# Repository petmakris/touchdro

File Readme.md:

# Parts

* ESP32 DEVKIT V1
    - https://www.aliexpress.us/item/2255800094862861.html

* Micro USB Connector Breakout 

  - https://www.aliexpress.com/item/1005006088838882.html

* ±5% 100V 100nF -40℃~+110℃ Metallized Polyester Plugin,P=5mm

    - [C3034534](https://www.lcsc.com/product-detail/Film-Capacitors_KNSCHA-MEB104J100V82CB0018_C3034534.html)

* 47uF 50V ±20% 180mA@100kHz Plugin,D6.3xL12mm 

    - [C2831773](https://www.lcsc.com/product-detail/Aluminum-Electrolytic-Capacitors-Leaded_KNSCHA-03EC0571_C2831773.html)

* Metal Film Resistors 4.7kΩ 250mW ±100ppm/℃ ±1%
 
    - [C119339](https://www.lcsc.com/product-detail/Through-Hole-Resistors_CCO-Chian-Chia-Elec-MF1-4W-4-7K-1-T_C119339.html)

* Metal Film Resistors 47kΩ 250mW ±50ppm/℃ ±1%

    - [C410613](https://www.lcsc.com/product-detail/Through-Hole-Resistors_TyoHM-RN-1-4W-47K-F-T-B-A1_C410613.html)

* SN74HC14N Schmitt Trigger 6 21ns@6V,50pF 2uA 2V~6V DIP-14 Inverters ROHS

    - [C2907](https://www.lcsc.com/product-detail/Inverters_Texas-Instruments-SN74HC14N_C2907.html)

# Micro USB Breakout

# ESP32 DevKit V1

# Firmware

```bash
esptool.py --chip esp32 --port COM5 --baud 460800 --before default_reset --after hard_reset write_flash --flash_mode dio --flash_size detect --flash_freq 40m 0x1000 bootloader.bin 0x8000 partition-table.bin 0x10000 touchdro-diy-universal-1.6.bin
```

It seems that for the esp32 to broadcast you need to keep the boot 
button pressed

# References

- https://www.touchdro.com/resources/adapters/diy/esp32-diy-dro.html
- https://gitlab.com/VictorLamoine/kicad

https://www.touchdro.com/resources/adapters/diy/esp32-diy-dro.html

# Ordering from JLCPCB

## Step 1

from within `PCB`: 

- Export Gerber files
- Export Drill Files

- Export Placement file
  - Separate files for front/back
  - Keep only top file
  - Remove components not to be mounted

## Step 2 

from within `Schematic`:

Create BOM compatible with JLCPCB the custom plugin from within our `kicad-libs` projecs:

This plugin will include only the components with a `JLCPCB` attributes

# Production files

kicad_pos_to_cpl.py POSITION.POSITION-JLCPCB.csv overrides.json [overrides.json]

## Tune placement file

Example `overrides.json`:

```json
{
    "D3": 180,
    "Q1": 180,

    "U6": -90,
    "U8": -90
}
```

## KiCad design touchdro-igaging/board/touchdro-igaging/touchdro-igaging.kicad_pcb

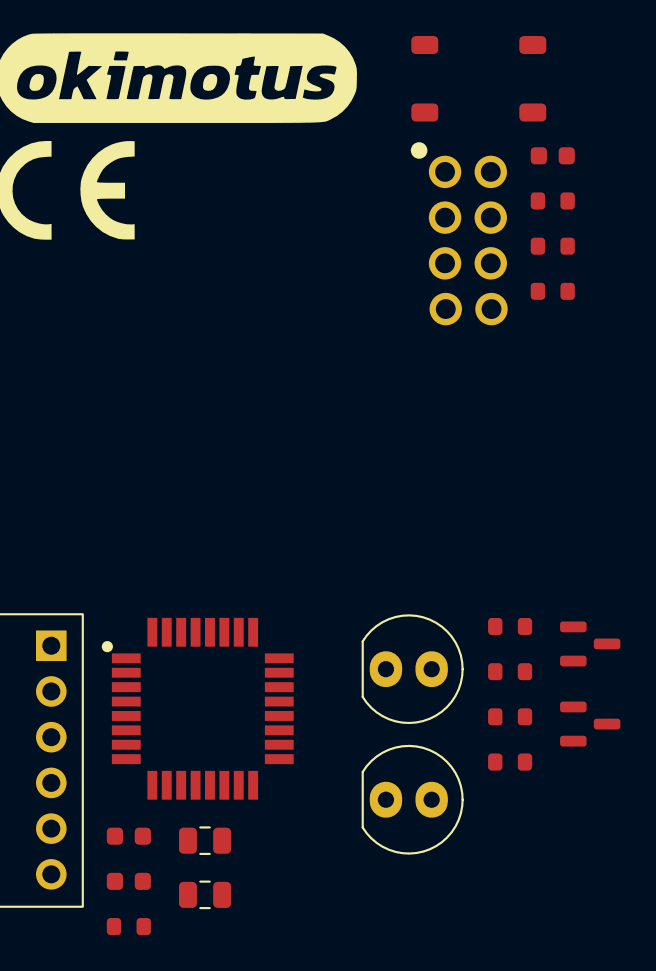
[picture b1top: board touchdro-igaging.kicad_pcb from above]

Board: 4 copper layers, 27 parts (0 on the bottom side), 12 nets, no tracks yet.

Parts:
C5, C7: 0805_10uF; C_0805
C6, C8, C35: 0603_100nF; C_0603
G1: CE 8mm; ce-8mm
G2: Okimotus Logo; okimotus-logo-20mm
H7, H8, H9, H10: Screw-3.2mm; ScrewHole-3.2mm
ISP1: AVR_ISP_8pin; AVR_ISP_8pin_VCC
LED1: LED_TH_5mm_Green; LED_D5.0mm_Green
LED2: LED_TH_5mm_Red; LED_D5.0mm_Red
Q2, Q3: AO3400A
R3, R48, R49: 0603_100; R_0603
R47: 0603_4K7; R_0603
R56, R58: 0603_470; R_0603
R57, R59: 0603_10K; R_0603
SW1: TS-1187A-B-A-B
U1: ATMEGA328PB-AU
U2: HC05

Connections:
/AVCC: C7.1, C8.1, R3.2, U1.18 (AVCC)
/LED_{1}: Q2.G, R57.1
/LED_{2}: Q3.G, R59.1
/~RESET: C35.1, R47.2, R48.1, R49.2, U1.29 (nRESET__[22]__PC6)
GND: C5.2, C6.2, C7.2, C8.2, C35.2, ISP1.GND, Q2.S, Q3.S, R57.2, R59.2, SW1.1, U1.5 (GND), U1.21 (GND)
unnamed: ISP1.RST, R48.2
unnamed: LED1.C, R56.2
unnamed: LED2.C, R58.2
unnamed: Q2.D, R56.1
unnamed: Q3.D, R58.1
unnamed: R49.1, SW1.2
VCC: C5.1, C6.1, ISP1.VCC, LED1.A, LED2.A, R3.1, R47.1, U1.4 (VCC)

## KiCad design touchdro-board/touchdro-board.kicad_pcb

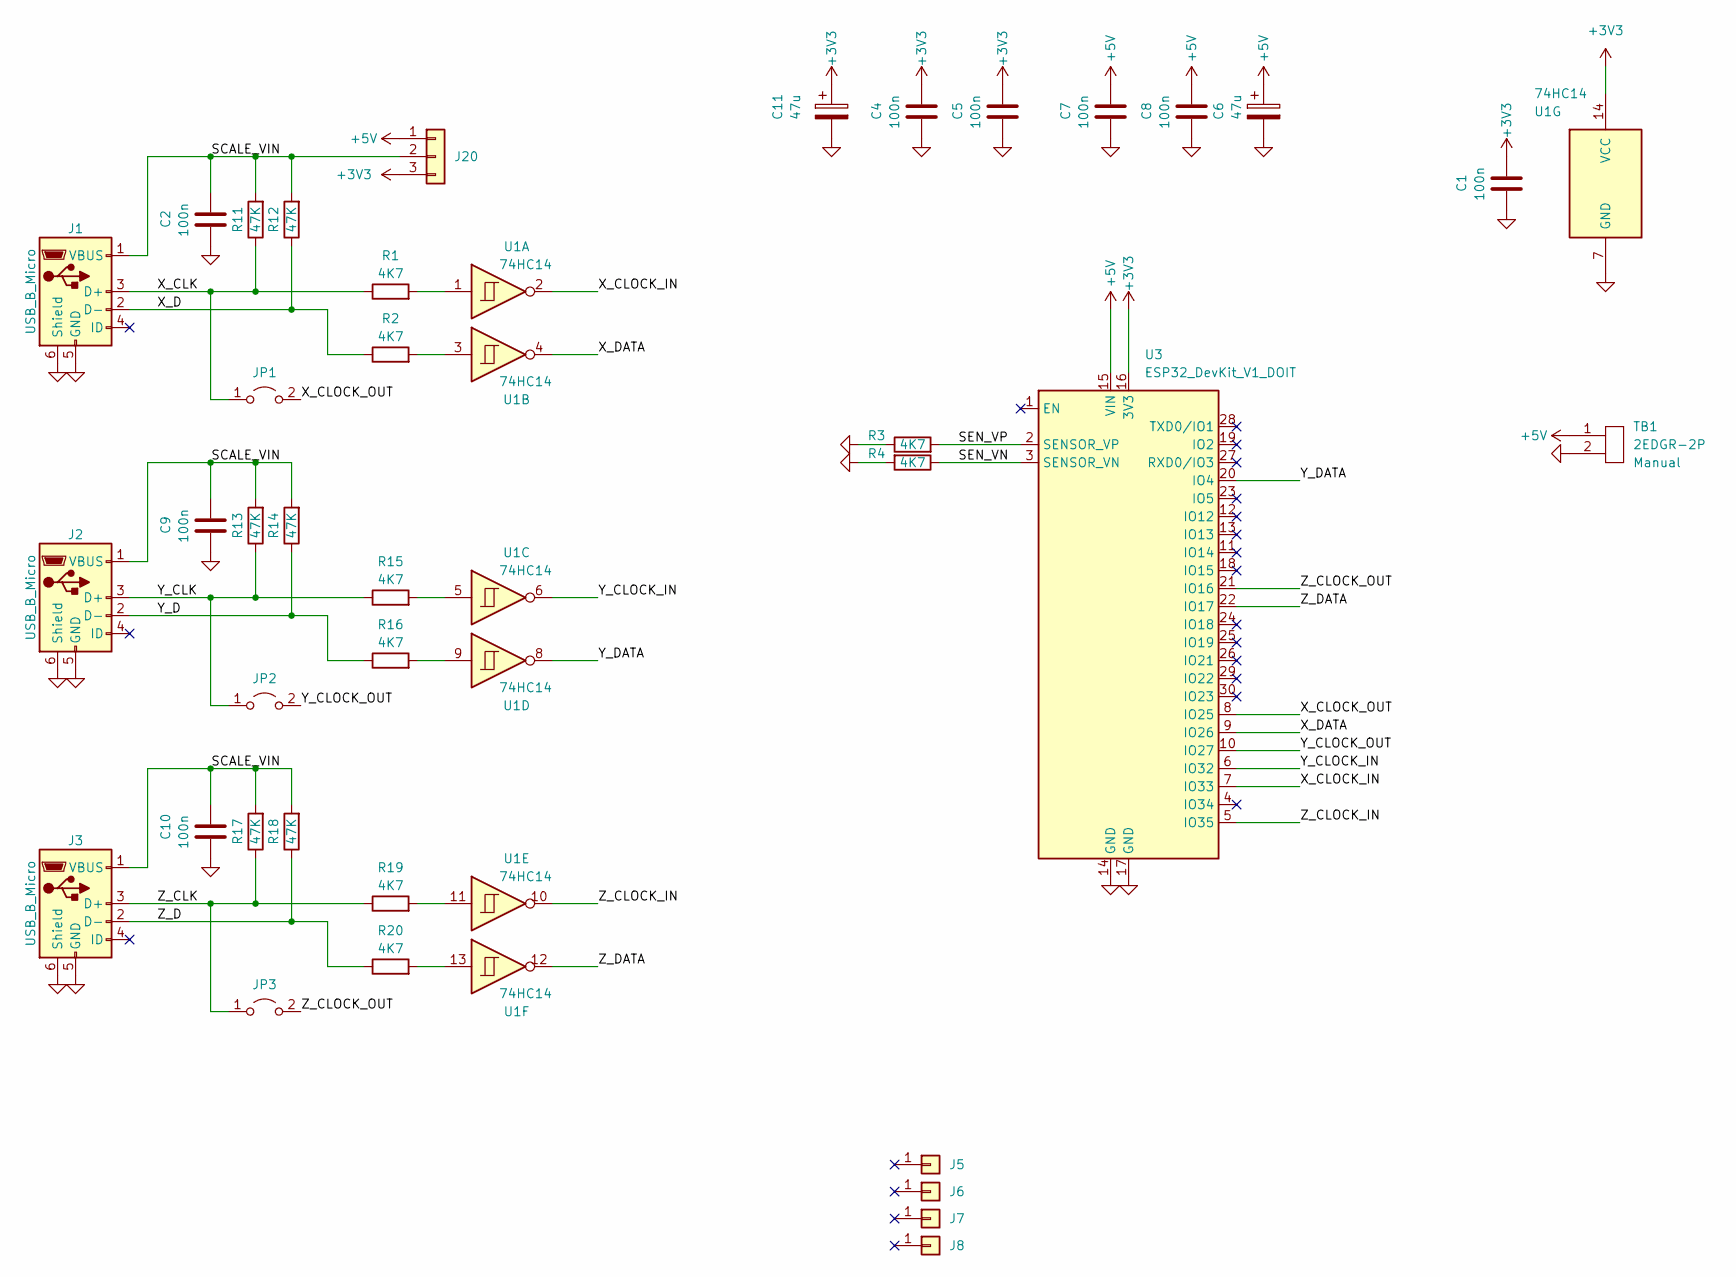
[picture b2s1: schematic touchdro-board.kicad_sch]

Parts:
C1, C2, C4, C5, C7, C8, C9, C10: 100n; C_Rect_L7.2mm_W3.0mm_P5.00mm_FKS2_FKP2_MKS2_MKP2; LCSC C3034534
C6, C11: 47u; CP_Radial_D8.0mm_P3.50mm; LCSC 03EC0571
J1, J2, J3: USB_B_Micro; MicroUSB
J5, J6, J7, J8: Conn_01x01; MountingHole_3.5mm
J20: Conn_01x03; PinHeader_1x03_P2.54mm_Vertical
JP1, JP2, JP3: Jumper_2_Open; PinHeader_1x02_P2.54mm_Vertical
R1, R2, R3, R4, R15, R16, R19, R20: 4K7; R_Axial_DIN0207_L6.3mm_D2.5mm_P7.62mm_Horizontal; LCSC C119339
R11, R12, R13, R14, R17, R18: 47K; R_Axial_DIN0207_L6.3mm_D2.5mm_P7.62mm_Horizontal; LCSC C410613
TB1: 2EDGR-2P
U1: 74HC14; DIP-14_W7.62mm; LCSC C2907
U3: ESP32_DevKit_V1_DOIT; esp32_devkit_v1_doit

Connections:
+3V3: C1.1, C4.1, C5.1, C11.1, J20.3, U1.14 (VCC), U3.16 (3V3)
+5V: C6.1, C7.1, C8.1, J20.1, TB1.1, U3.15 (VIN)
/SCALE_VIN: C2.1, C9.1, C10.1, J1.1 (VBUS), J2.1 (VBUS), J3.1 (VBUS), J20.2, R11.2, R12.2, R13.2, R14.2, R17.2, R18.2
/SEN_VN: R4.1, U3.3 (SENSOR_VN)
/SEN_VP: R3.2, U3.2 (SENSOR_VP)
/X_CLK: J1.3 (D+), JP1.1 (A), R1.1, R11.1
/X_CLOCK_IN: U1.2, U3.7 (IO33)
/X_CLOCK_OUT: JP1.2 (B), U3.8 (IO25)
/X_D: J1.2 (D-), R2.1, R12.1
/X_DATA: U1.4, U3.9 (IO26)
/Y_CLK: J2.3 (D+), JP2.1 (A), R13.1, R15.1
/Y_CLOCK_IN: U1.6, U3.6 (IO32)
/Y_CLOCK_OUT: JP2.2 (B), U3.10 (IO27)
/Y_D: J2.2 (D-), R14.1, R16.1
/Y_DATA: U1.8, U3.20 (IO4)
/Z_CLK: J3.3 (D+), JP3.1 (A), R17.1, R19.1
/Z_CLOCK_IN: U1.10, U3.5 (IO35)
/Z_CLOCK_OUT: JP3.2 (B), U3.21 (IO16)
/Z_D: J3.2 (D-), R18.1, R20.1
/Z_DATA: U1.12, U3.22 (IO17)
GND: C1.2, C2.2, C4.2, C5.2, C6.2, C7.2, C8.2, C9.2, C10.2, C11.2, J1.5 (GND), J1.6 (Shield), J2.5 (GND), J2.6 (Shield), J3.5 (GND), J3.6 (Shield), R3.1, R4.2, TB1.2, U1.7 (GND), U3.14 (GND), U3.17 (GND)
unnamed: R1.2, U1.1
unnamed: R2.2, U1.3
unnamed: R15.2, U1.5
unnamed: R16.2, U1.9
unnamed: R19.2, U1.11
unnamed: R20.2, U1.13

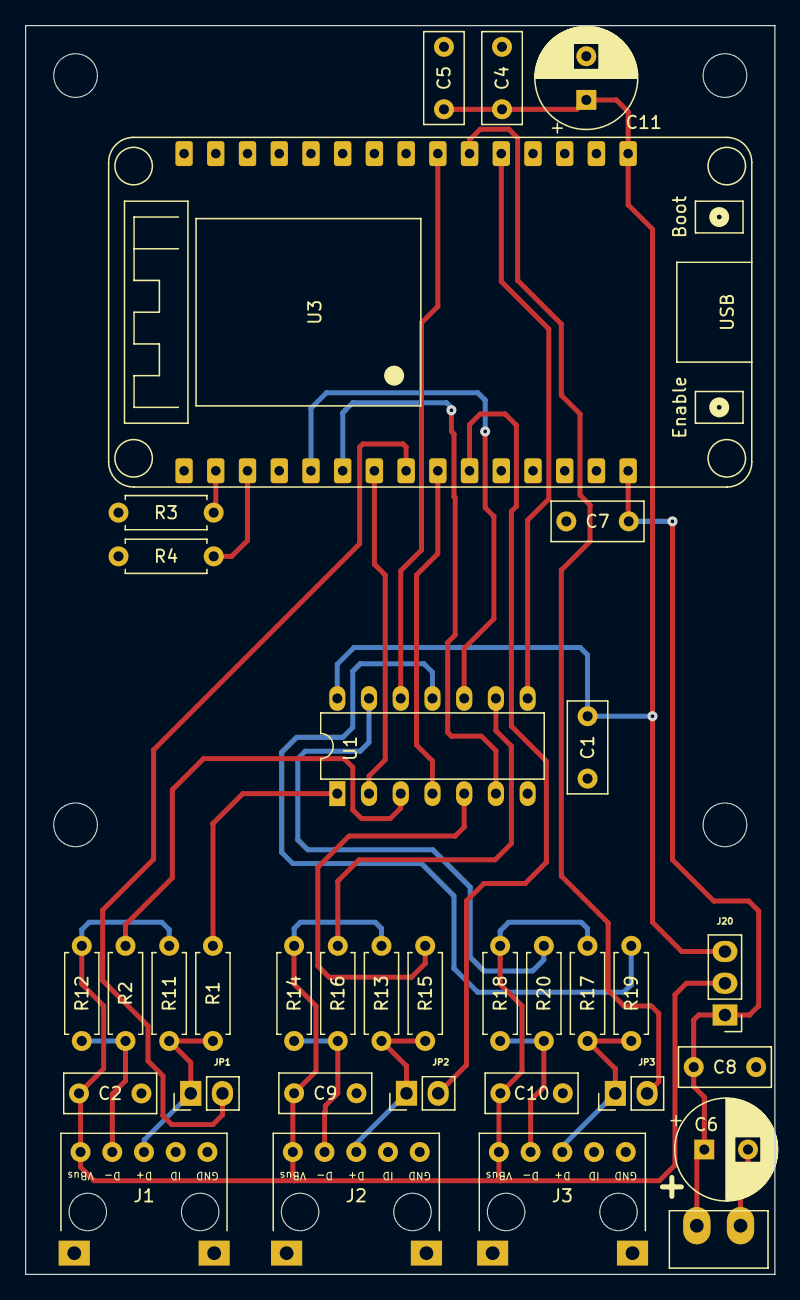
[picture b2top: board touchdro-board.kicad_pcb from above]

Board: 2 copper layers, 60.0 x 100.0 mm, 38 parts (0 on the bottom side), 27 nets.

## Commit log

2024-03-05 new placement
2024-03-08 updates:
